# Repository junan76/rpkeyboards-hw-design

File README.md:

# rpkeyboards-hw-degisn

## Introduction

The PCB design and 3d models of [rpkeyboards/mini](https://github.com/junan76/rpkeyboards).

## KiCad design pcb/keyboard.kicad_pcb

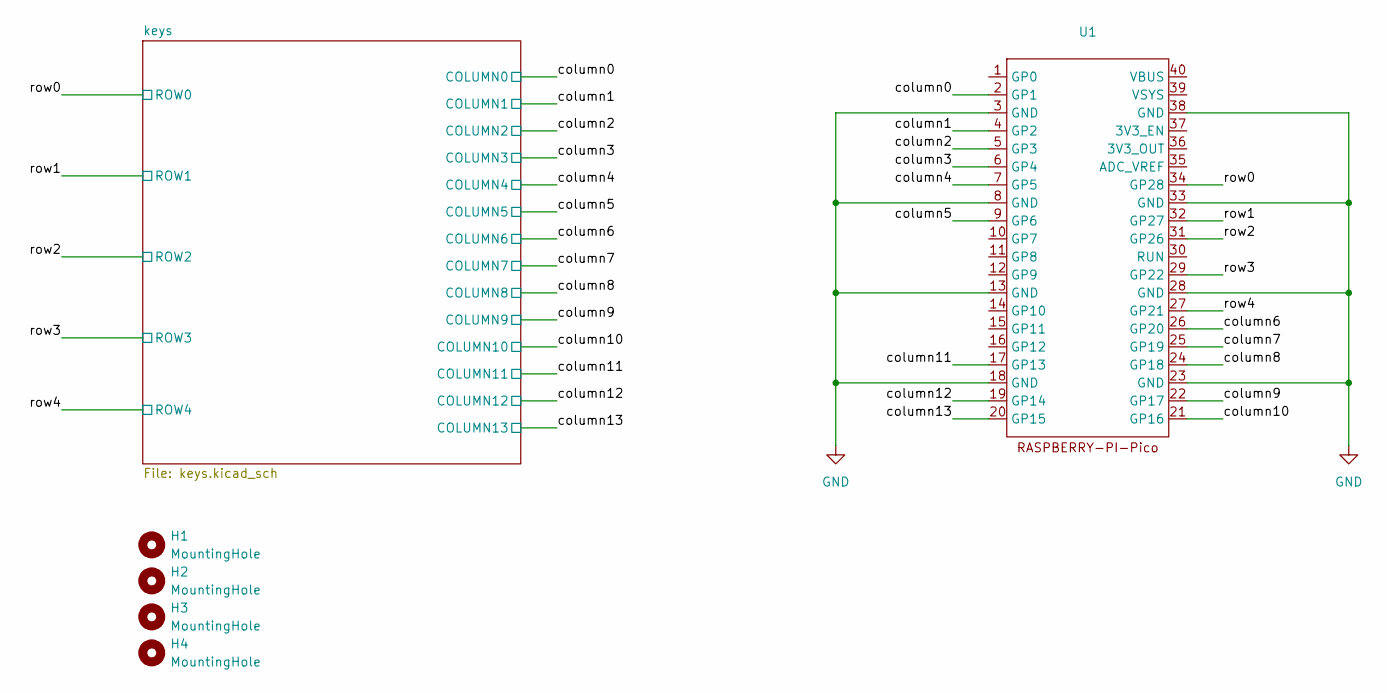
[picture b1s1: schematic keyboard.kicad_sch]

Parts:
H1, H2, H3, H4: MountingHole; MountingHole_3.2mm_M3
U1: raspberry_pi_pico

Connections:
/column0: U1.2 (GP1); also elsewhere on the board
/column1: U1.4 (GP2); also elsewhere on the board
/column2: U1.5 (GP3); also elsewhere on the board
/column3: U1.6 (GP4); also elsewhere on the board
/column4: U1.7 (GP5); also elsewhere on the board
/column5: U1.9 (GP6); also elsewhere on the board
/column6: U1.26 (GP20); also elsewhere on the board
/column7: U1.25 (GP19); also elsewhere on the board
/column8: U1.24 (GP18); also elsewhere on the board
/column9: U1.22 (GP17); also elsewhere on the board
/column10: U1.21 (GP16); also elsewhere on the board
/column11: U1.17 (GP13); also elsewhere on the board
/column12: U1.19 (GP14); also elsewhere on the board
/column13: U1.20 (GP15); also elsewhere on the board
/row0: U1.34 (GP28); also elsewhere on the board
/row1: U1.32 (GP27); also elsewhere on the board
/row2: U1.31 (GP26); also elsewhere on the board
/row3: U1.29 (GP22); also elsewhere on the board
/row4: U1.27 (GP21); also elsewhere on the board
GND: U1.3 (GND), U1.8 (GND), U1.13 (GND), U1.18 (GND), U1.23 (GND), U1.28 (GND), U1.33 (GND), U1.38 (GND)

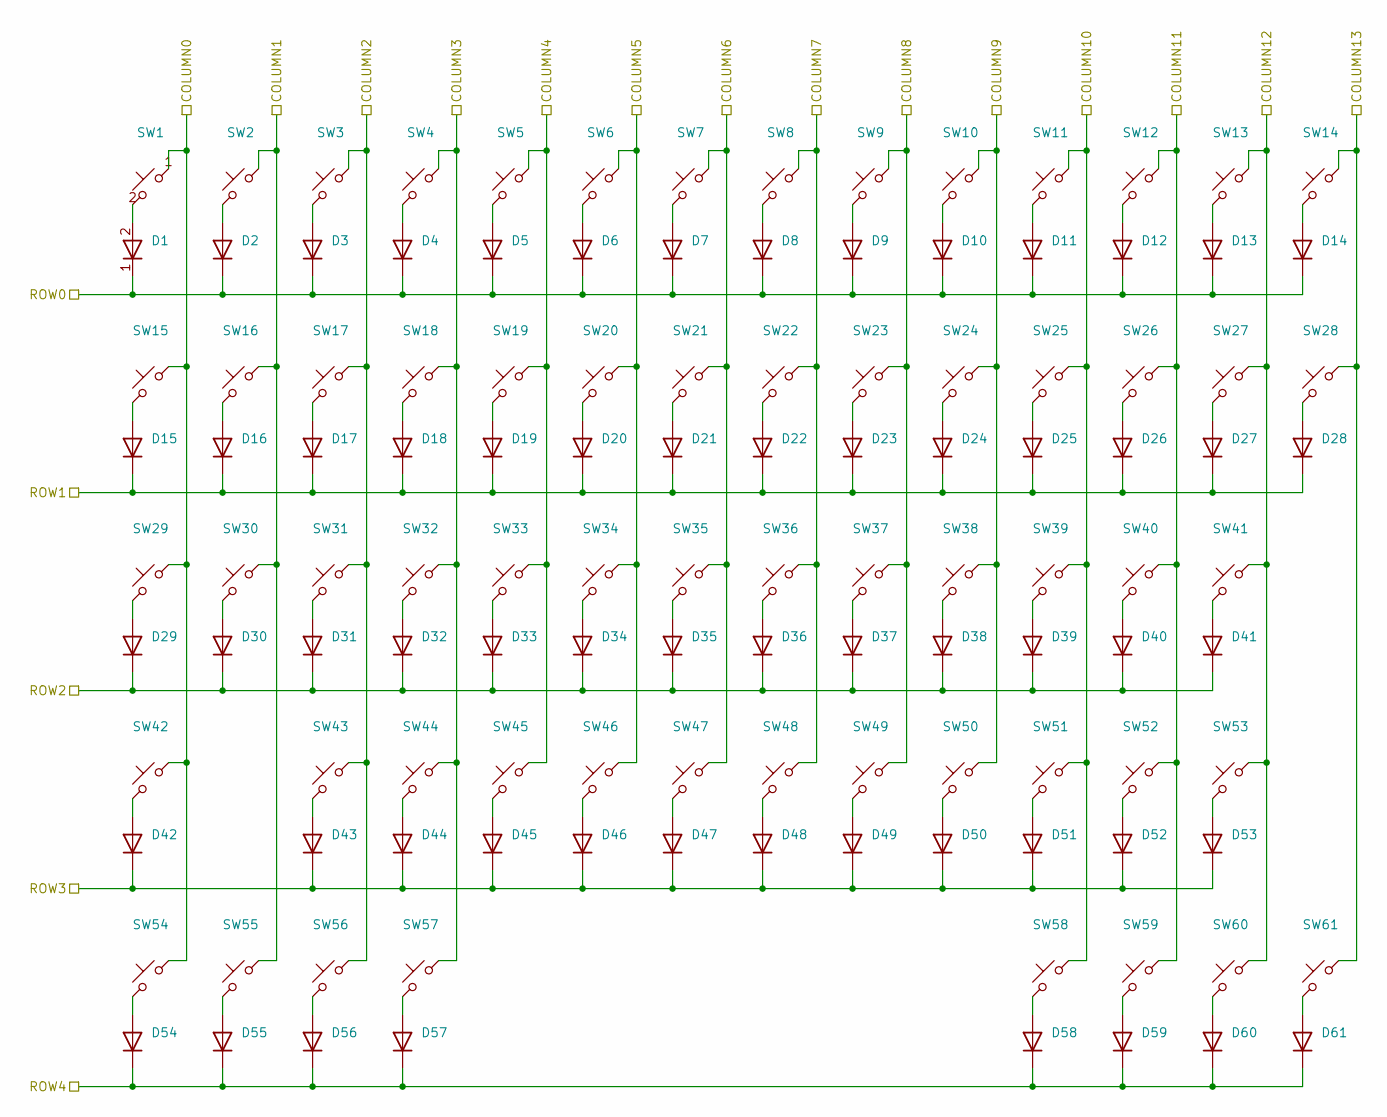
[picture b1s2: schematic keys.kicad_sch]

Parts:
D1, D2, D3, D4, D5, D6, D7, D8, D9, D10, D11, D12, D13, D14, D15, D16, D17, D18, D19, D20, D21, D22, D23, D24, D25, D26, D27, D28, D29, D30, D31, D32, D33, D34, D35, D36, D37, D38, D39, D40, D41, D42, D43, D44, D45, D46, D47, D48, D49, D50, D51, D52, D53, D54, D55, D56, D57, D58, D59, D60, D61: D; D_0805_2012Metric
SW1, SW2, SW3, SW4, SW5, SW6, SW7, SW8, SW9, SW10, SW11, SW12, SW13, SW16, SW17, SW18, SW19, SW20, SW21, SW22, SW23, SW24, SW25, SW26, SW27, SW30, SW31, SW32, SW33, SW34, SW35, SW36, SW37, SW38, SW39, SW40, SW43, SW44, SW45, SW46, SW47, SW48, SW49, SW50, SW51, SW52: SW_Push_45deg; SW_Cherry_MX_1.00u_PCB
SW14: SW_Push_45deg; SW_Cherry_MX_2.00u_PCB
SW15, SW28: SW_Push_45deg; SW_Cherry_MX_1.50u_PCB
SW29: SW_Push_45deg; SW_Cherry_MX_1.75u_PCB
SW41, SW42: SW_Push_45deg; SW_Cherry_MX_2.25u_PCB
SW53: SW_Push_45deg; SW_Cherry_MX_2.75u_PCB
SW54, SW55, SW56, SW58, SW59, SW60, SW61: SW_Push_45deg; SW_Cherry_MX_1.25u_PCB
SW57: SW_Push_45deg; SW_Cherry_MX_6.25u_PCB

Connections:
/column0: SW1.1, SW15.1, SW29.1, SW42.1, SW54.1; also elsewhere on the board
/column1: SW2.1, SW16.1, SW30.1, SW55.1; also elsewhere on the board
/column2: SW3.1, SW17.1, SW31.1, SW43.1, SW56.1; also elsewhere on the board
/column3: SW4.1, SW18.1, SW32.1, SW44.1, SW57.1; also elsewhere on the board
/column4: SW5.1, SW19.1, SW33.1, SW45.1; also elsewhere on the board
/column5: SW6.1, SW20.1, SW34.1, SW46.1; also elsewhere on the board
/column6: SW7.1, SW21.1, SW35.1, SW47.1; also elsewhere on the board
/column7: SW8.1, SW22.1, SW36.1, SW48.1; also elsewhere on the board
/column8: SW9.1, SW23.1, SW37.1, SW49.1; also elsewhere on the board
/column9: SW10.1, SW24.1, SW38.1, SW50.1; also elsewhere on the board
/column10: SW11.1, SW25.1, SW39.1, SW51.1, SW58.1; also elsewhere on the board
/column11: SW12.1, SW26.1, SW40.1, SW52.1, SW59.1; also elsewhere on the board
/column12: SW13.1, SW27.1, SW41.1, SW53.1, SW60.1; also elsewhere on the board
/column13: SW14.1, SW28.1, SW61.1; also elsewhere on the board
/row0: D1.1 (K), D2.1 (K), D3.1 (K), D4.1 (K), D5.1 (K), D6.1 (K), D7.1 (K), D8.1 (K), D9.1 (K), D10.1 (K), D11.1 (K), D12.1 (K), D13.1 (K), D14.1 (K); also elsewhere on the board
/row1: D15.1 (K), D16.1 (K), D17.1 (K), D18.1 (K), D19.1 (K), D20.1 (K), D21.1 (K), D22.1 (K), D23.1 (K), D24.1 (K), D25.1 (K), D26.1 (K), D27.1 (K), D28.1 (K); also elsewhere on the board
/row2: D29.1 (K), D30.1 (K), D31.1 (K), D32.1 (K), D33.1 (K), D34.1 (K), D35.1 (K), D36.1 (K), D37.1 (K), D38.1 (K), D39.1 (K), D40.1 (K), D41.1 (K); also elsewhere on the board
/row3: D42.1 (K), D43.1 (K), D44.1 (K), D45.1 (K), D46.1 (K), D47.1 (K), D48.1 (K), D49.1 (K), D50.1 (K), D51.1 (K), D52.1 (K), D53.1 (K); also elsewhere on the board
/row4: D54.1 (K), D55.1 (K), D56.1 (K), D57.1 (K), D58.1 (K), D59.1 (K), D60.1 (K), D61.1 (K); also elsewhere on the board
unnamed: D1.2 (A), SW1.2
unnamed: D2.2 (A), SW2.2
unnamed: D3.2 (A), SW3.2
unnamed: D4.2 (A), SW4.2
unnamed: D5.2 (A), SW5.2
unnamed: D6.2 (A), SW6.2
unnamed: D7.2 (A), SW7.2
unnamed: D8.2 (A), SW8.2
unnamed: D9.2 (A), SW9.2
unnamed: D10.2 (A), SW10.2
unnamed: D11.2 (A), SW11.2
unnamed: D12.2 (A), SW12.2
unnamed: D13.2 (A), SW13.2
unnamed: D14.2 (A), SW14.2
unnamed: D15.2 (A), SW15.2
unnamed: D16.2 (A), SW16.2
unnamed: D17.2 (A), SW17.2
unnamed: D18.2 (A), SW18.2
unnamed: D19.2 (A), SW19.2
unnamed: D20.2 (A), SW20.2
unnamed: D21.2 (A), SW21.2
unnamed: D22.2 (A), SW22.2
unnamed: D23.2 (A), SW23.2
unnamed: D24.2 (A), SW24.2
unnamed: D25.2 (A), SW25.2
unnamed: D26.2 (A), SW26.2
unnamed: D27.2 (A), SW27.2
unnamed: D28.2 (A), SW28.2
unnamed: D29.2 (A), SW29.2
unnamed: D30.2 (A), SW30.2
unnamed: D31.2 (A), SW31.2
unnamed: D32.2 (A), SW32.2
unnamed: D33.2 (A), SW33.2
unnamed: D34.2 (A), SW34.2
unnamed: D35.2 (A), SW35.2
unnamed: D36.2 (A), SW36.2
unnamed: D37.2 (A), SW37.2
unnamed: D38.2 (A), SW38.2
unnamed: D39.2 (A), SW39.2
unnamed: D40.2 (A), SW40.2
unnamed: D41.2 (A), SW41.2
unnamed: D42.2 (A), SW42.2
unnamed: D43.2 (A), SW43.2
unnamed: D44.2 (A), SW44.2
unnamed: D45.2 (A), SW45.2
unnamed: D46.2 (A), SW46.2
unnamed: D47.2 (A), SW47.2
unnamed: D48.2 (A), SW48.2
unnamed: D49.2 (A), SW49.2
unnamed: D50.2 (A), SW50.2
unnamed: D51.2 (A), SW51.2
unnamed: D52.2 (A), SW52.2
unnamed: D53.2 (A), SW53.2
unnamed: D54.2 (A), SW54.2
unnamed: D55.2 (A), SW55.2
unnamed: D56.2 (A), SW56.2
unnamed: D57.2 (A), SW57.2
unnamed: D58.2 (A), SW58.2
unnamed: D59.2 (A), SW59.2
unnamed: D60.2 (A), SW60.2
unnamed: D61.2 (A), SW61.2

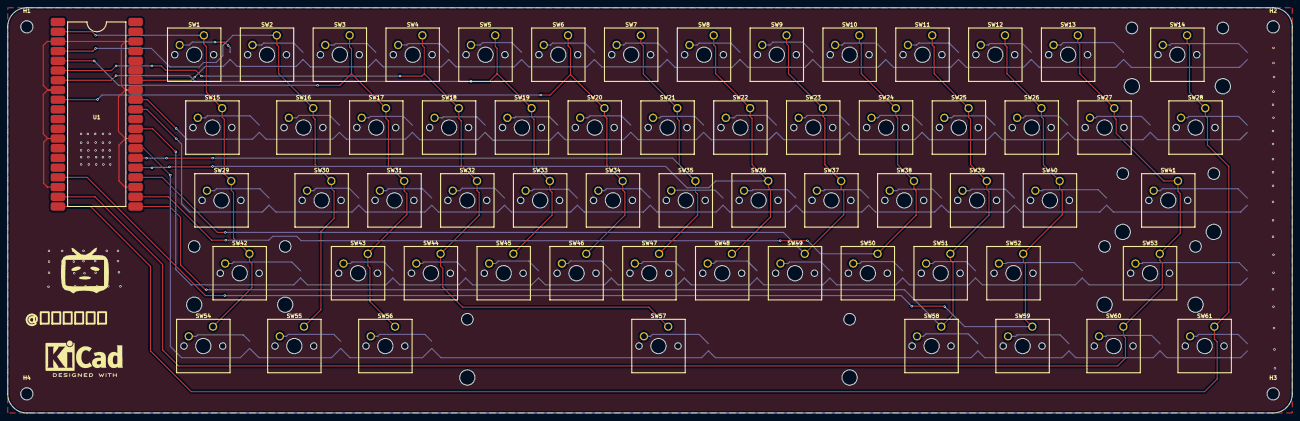
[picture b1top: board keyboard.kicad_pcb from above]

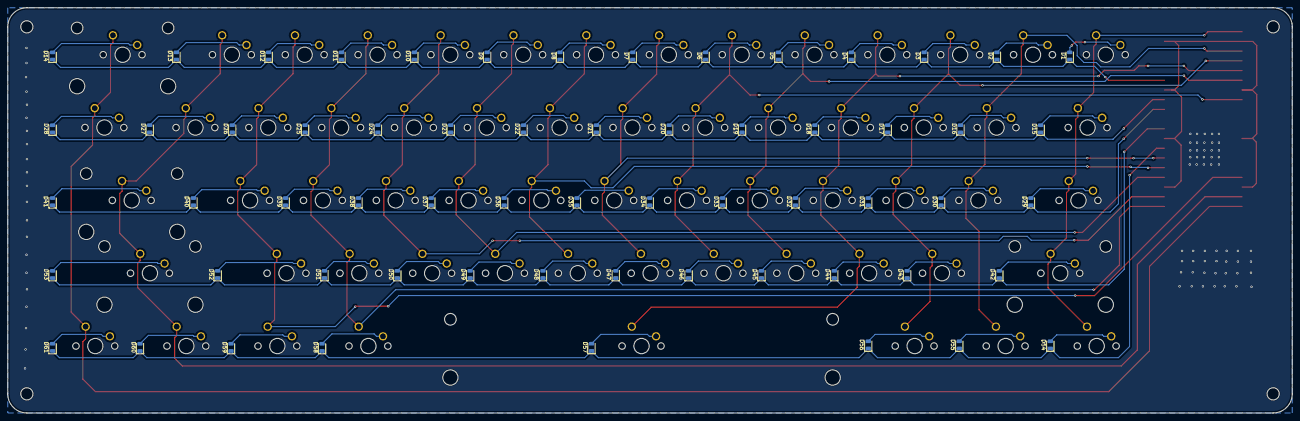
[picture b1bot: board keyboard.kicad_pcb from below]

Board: 2 copper layers, 336.0 x 106.0 mm, 127 parts (61 on the bottom side), 81 nets.

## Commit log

2025-01-20 [dev]: upload the pcb design and 3d-model files.
